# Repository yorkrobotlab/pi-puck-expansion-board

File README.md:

# YRL Expansion Board for the Pi-puck

**An expansion board for the Pi-puck robot platform, including an IMU, XBee socket, navigation switch, RGB LED, and 24-pin Raspberry Pi compatible header.**

See https://github.com/yorkrobotlab/pi-puck for more information on the Pi-puck.

## PCB Layout

## XBee

Scripts to set up the XBee hardware and update the firmware are in [xbee/](xbee/).
Requires the Digi XBee Python Library (see https://github.com/digidotcom/xbee-python).

## Licence

Hardware designs are licensed under a [Creative Commons Attribution-ShareAlike 4.0 International Licence][cc-by-sa].

Unless otherwise specified, software is licensed under an [MIT Licence][mit].

[cc-by-sa]: http://creativecommons.org/licenses/by-sa/4.0/
[mit]: /LICENSE-MIT

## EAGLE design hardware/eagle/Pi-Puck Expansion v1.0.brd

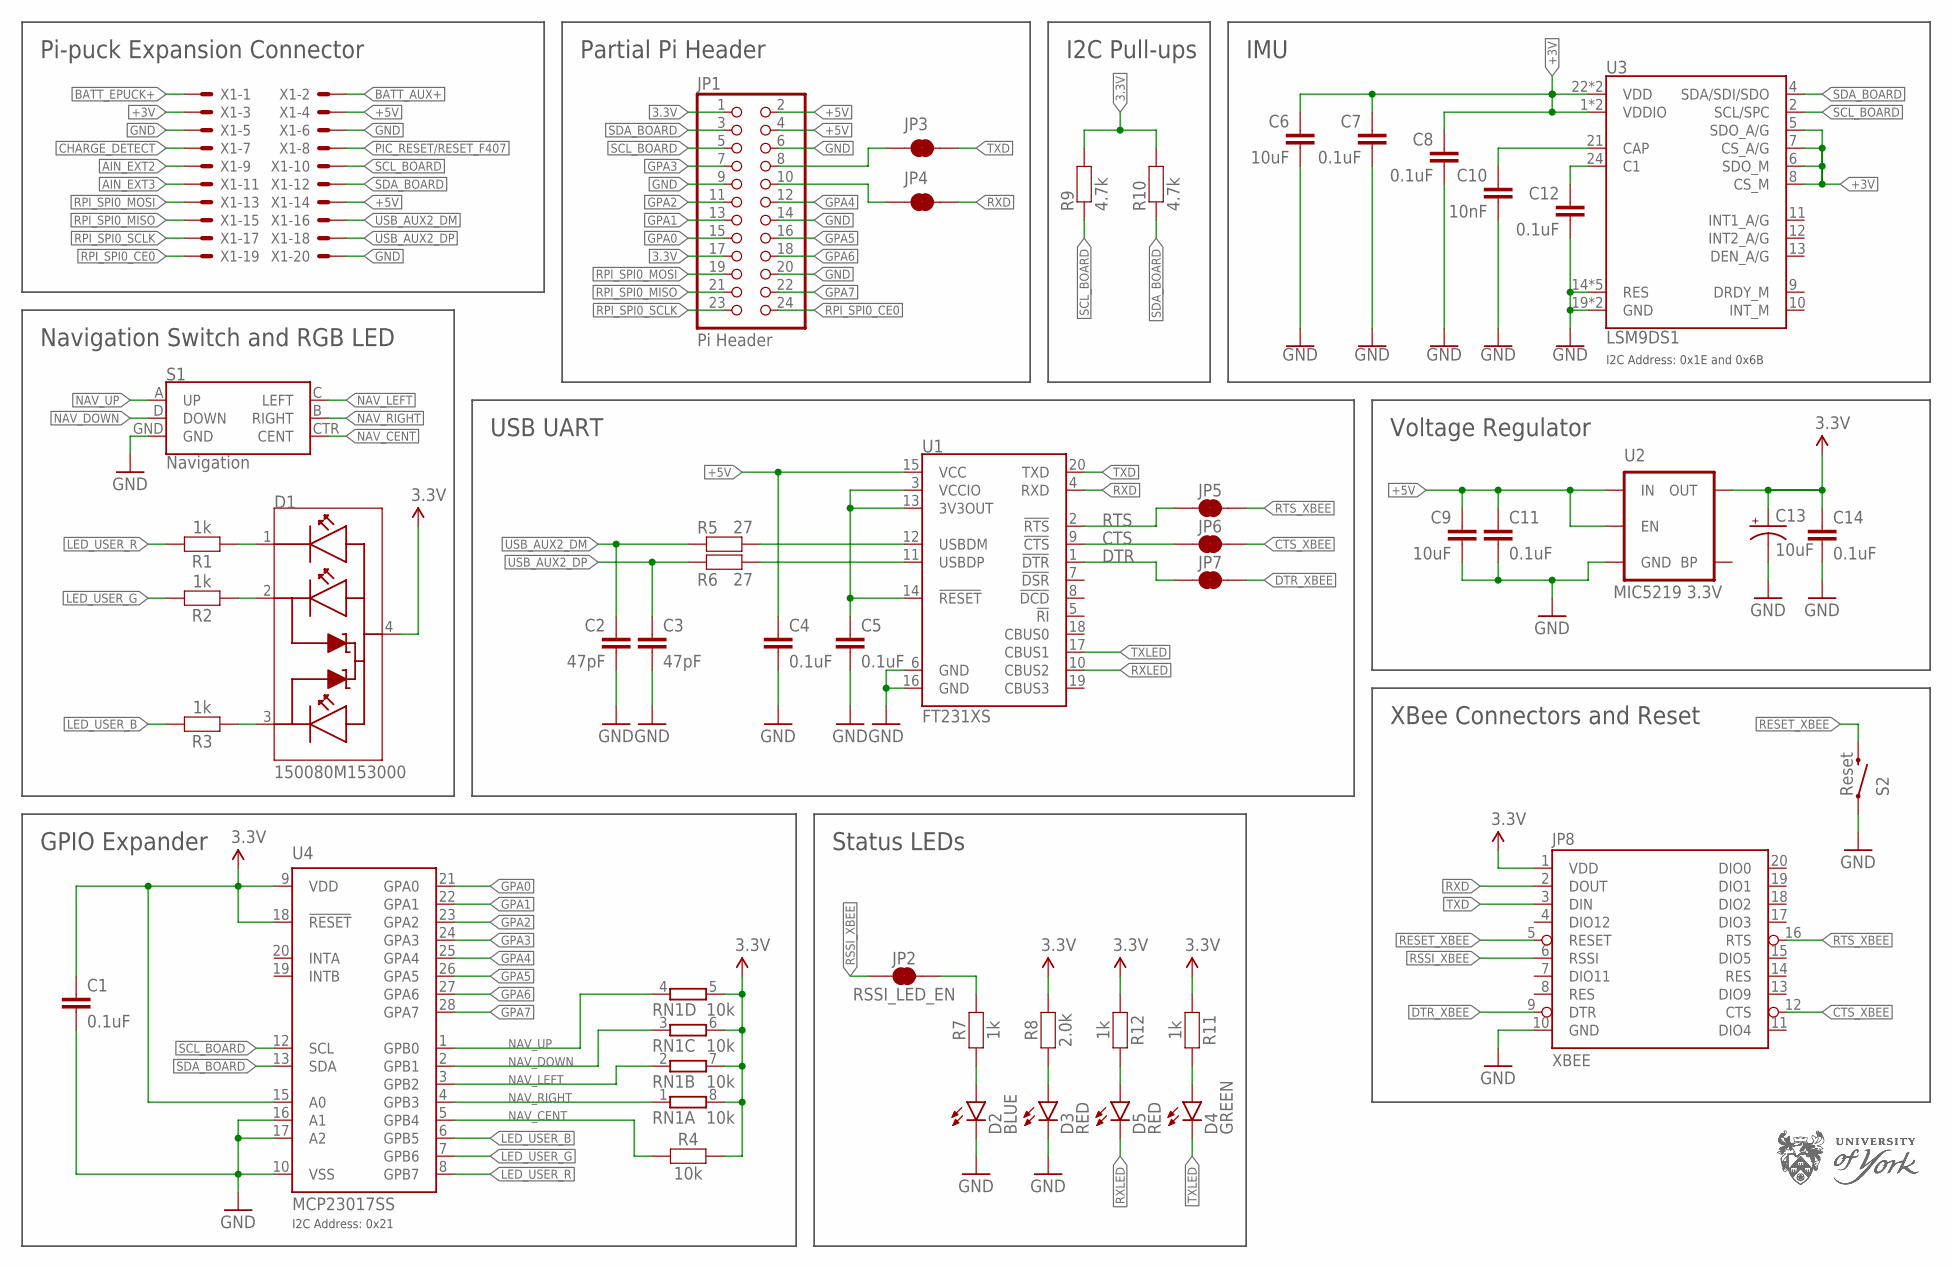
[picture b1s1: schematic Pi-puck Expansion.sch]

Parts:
C1, C4, C5, C7, C8, C11, C12, C14: 0.1uF; 0603
C2, C3: 47pF; 0603
C6, C9: 10uF; 0805
C10: 10nF; 0603
C13: 10uF; EIA3216
D1: 150080M153000; LED_150080M153000
D2: BLUE; LED-0603
D3, D5: RED; LED-0603
D4: GREEN; LED-0603
JP1: Pi Header; 2X12
JP2: RSSI_LED_EN; SMT-JUMPER_2_NC_TRACE_SILK
JP3: TXD; SMT-JUMPER_2_NC_TRACE_SILK
JP4: RXD; SMT-JUMPER_2_NC_TRACE_SILK
JP5: CTS_EN; SMT-JUMPER_2_NC_TRACE_SILK
JP6: RTS_EN; SMT-JUMPER_2_NC_TRACE_SILK
JP7: DTR; SMT-JUMPER_2_NC_TRACE_SILK
JP8: XBEE; XBEE-SILK
LOGO1: UOY-LOGO-30MM; UOY-LOGO-30MM-WIDE
LOGO2: UOY-LOGO-10MM; UOY-LOGO-10MM-WIDE
R1, R2, R3, R7, R11, R12: 1k; 0603
R4: 10k; 0603
R5, R6: 27; 0603
R8: 2.0k; 0603
R9, R10: 4.7k; 0603
RN1: 10k; EXBV8V
S1: Navigation; JOYSTICK_MINI
S2: Reset; TACTILE_SWITCH_SMD_4.6X2.8MM
U1: FT231XS; SSOP20_L
U2: MIC5219 3.3V; SOT23-5
U3: LSM9DS1; LGA24-8X4
U4: MCP23017SS; SSOP28
X1: 87758-2016

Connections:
3.3V: C1.1, C13.+, C14.1, D1.4 (A), JP1.1, JP1.17, JP8.1 (VDD), R4.2, R8.2, R9.2, R10.2, R11.1, R12.1, RN1.5 (2), RN1.6 (2), RN1.7 (2), RN1.8 (2), U2.5 (OUT), U4.9 (VDD), U4.15 (A0), U4.18 (!RESET)
3V-INT: C5.1, U1.3 (VCCIO), U1.13 (3V3OUT), U1.14 (!RESET)
+3V: C6.1, C7.1, C8.1, U3.1 (VDDIO), U3.3 (VDDIO), U3.5 (SDO_A/G), U3.6 (SDO_M), U3.7 (CS_A/G), U3.8 (CS_M), U3.22 (VDD), U3.23 (VDD), X1.3
+5V: C4.1, C9.1, C11.1, JP1.2, JP1.4, U1.15 (VCC), U2.1 (IN), U2.3 (EN), X1.4, X1.14
AIN_EXT2: X1.9
AIN_EXT3: X1.11
BATT_AUX+: X1.2
BATT_EPUCK+: X1.1
C1: C12.1, U3.24 (C1)
CAP: C10.1, U3.21 (CAP)
CHARGE_DETECT: X1.7
CTS: JP6.1, U1.9 (!CTS)
CTS_XBEE: JP6.2, JP8.12 (CTS)
DTR: JP7.1, U1.1 (!DTR)
DTR_XBEE: JP7.2, JP8.9 (DTR)
GND: C1.2, C2.2, C3.2, C4.2, C5.2, C6.2, C7.2, C8.2, C9.2, C10.2, C11.2, C12.2, C13.-, C14.2, D2.C, D3.C, JP1.6, JP1.9, JP1.14, JP1.20, JP8.10 (GND), S1.GND, S2.1, S2.2 (1), U1.6 (GND), U1.16 (GND), U2.2 (GND), U3.14 (RES), U3.15 (RES), U3.16 (RES), U3.17 (RES), U3.18 (RES), U3.19 (GND), U3.20 (GND), U4.10 (VSS), U4.16 (A1), U4.17 (A2), X1.5, X1.6, X1.20
GPA0: JP1.15, U4.21 (GPA0)
GPA1: JP1.13, U4.22 (GPA1)
GPA2: JP1.11, U4.23 (GPA2)
GPA3: JP1.7, U4.24 (GPA3)
GPA4: JP1.12, U4.25 (GPA4)
GPA5: JP1.16, U4.26 (GPA5)
GPA6: JP1.18, U4.27 (GPA6)
GPA7: JP1.22, U4.28 (GPA7)
LED_USER_B: R3.2, U4.6 (GPB5)
LED_USER_G: R2.2, U4.7 (GPB6)
LED_USER_R: R1.2, U4.8 (GPB7)
unnamed: D5.A, R12.2
unnamed: JP1.8, JP3.1
unnamed: JP1.10, JP4.1
unnamed: D4.A, R11.2
unnamed: D1.1 (R), R1.1
unnamed: R6.2, U1.11 (USBDP)
unnamed: R5.2, U1.12 (USBDM)
unnamed: JP2.2, R7.2
unnamed: D1.2 (G), R2.1
unnamed: D1.3 (B), R3.1
unnamed: D3.A, R8.1
NAV_CENT: R4.1, S1.CTR (CENT), U4.5 (GPB4)
NAV_DOWN: RN1.3 (1), S1.D (DOWN), U4.2 (GPB1)
NAV_LEFT: RN1.2 (1), S1.C (LEFT), U4.3 (GPB2)
NAV_RIGHT: RN1.1, S1.B (RIGHT), U4.4 (GPB3)
NAV_UP: RN1.4 (1), S1.A (UP), U4.1 (GPB0)
PIC_RESET/RESET_F407: X1.8
RESET_XBEE: JP8.5 (RESET), S2.3 (2), S2.4 (2)
RPI_SPI0_CE0: JP1.24, X1.19
RPI_SPI0_MISO: JP1.21, X1.15
RPI_SPI0_MOSI: JP1.19, X1.13
RPI_SPI0_SCLK: JP1.23, X1.17
RSSILED: D2.A, R7.1
RSSI_XBEE: JP2.1, JP8.6 (RSSI)
RTS: JP5.1, U1.2 (!RTS)
RTS_XBEE: JP5.2, JP8.16 (RTS)
RXD: JP4.2, JP8.2 (DOUT), U1.4 (RXD)
RXLED: D5.C, U1.10 (CBUS2)
SCL_BOARD: JP1.5, R9.1, U3.2 (SCL/SPC), U4.12 (SCL), X1.10
SDA_BOARD: JP1.3, R10.1, U3.4 (SDA/SDI/SDO), U4.13 (SDA), X1.12
TXD: JP3.2, JP8.3 (DIN), U1.20 (TXD)
TXLED: D4.C, U1.17 (CBUS1)
USB_AUX2_DM: C2.1, R5.1, X1.16
USB_AUX2_DP: C3.1, R6.1, X1.18

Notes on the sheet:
Pi-puck Expansion Connector
Partial Pi Header
GPIO Expander
I2C Address: 0x21
Navigation Switch and RGB LED
I2C Address: 0x1E and 0x6B
Voltage Regulator
I2C Pull-ups
USB UART
IMU
XBee Connectors and Reset
Status LEDs

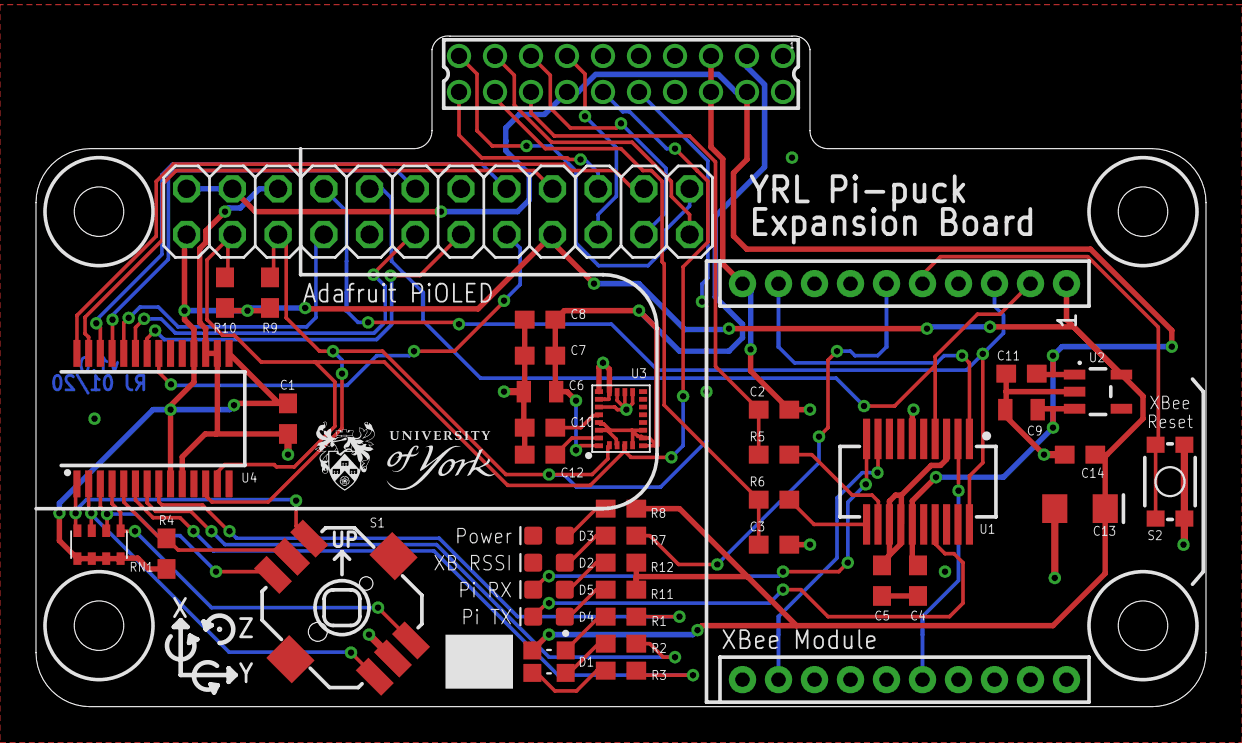
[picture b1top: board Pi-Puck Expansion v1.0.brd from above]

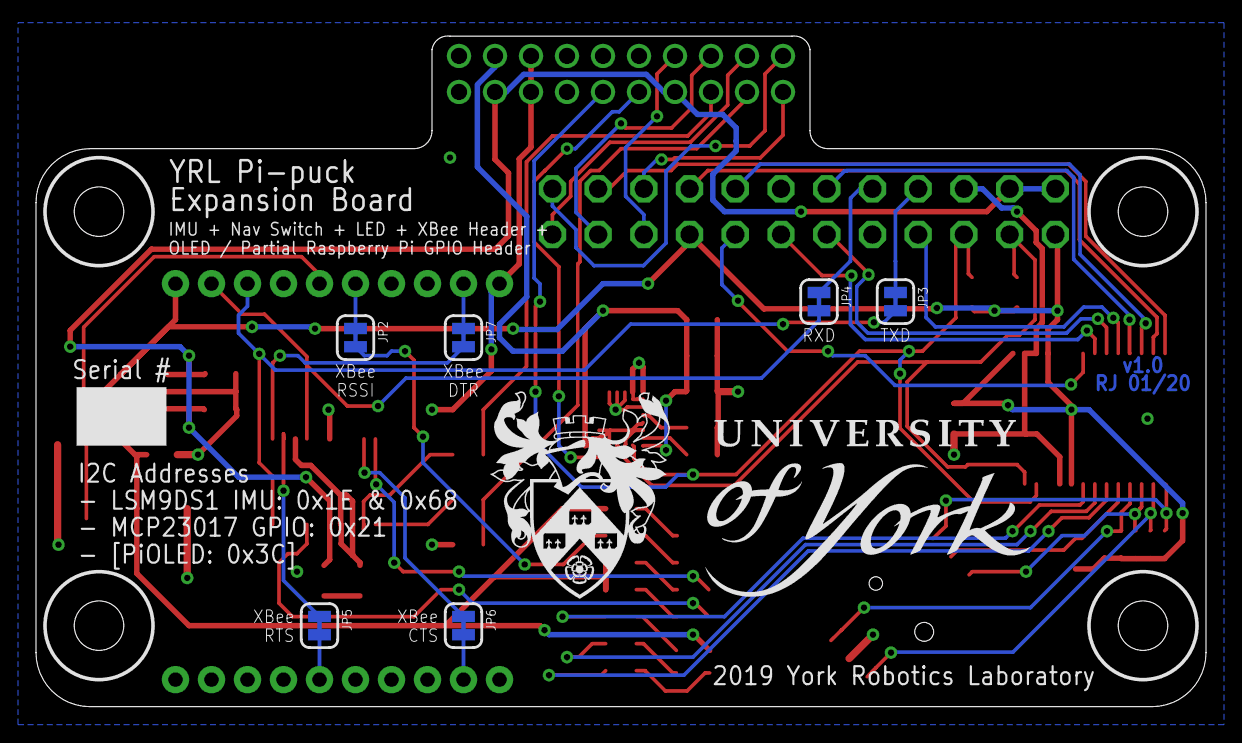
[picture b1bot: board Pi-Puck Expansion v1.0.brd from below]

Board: 2 copper layers, 65.0 x 37.3 mm, 49 parts (7 on the bottom side), 55 nets.

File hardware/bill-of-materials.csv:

Part,Value,Description,Package,Manufacturer,Manufacturer Part Number,Supplier,Order code,Notes,URL
C2,47p,Capacitor,0603,KEMET,C0603X470J1GACTU,Farnell,2905080,±5% C0G / NP0,https://uk.farnell.com/kemet/c0603x470j1gactu/cap-47pf-100v-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
C3,47p,Capacitor,0603,KEMET,C0603X470J1GACTU,Farnell,2905080,±5% C0G / NP0,https://uk.farnell.com/kemet/c0603x470j1gactu/cap-47pf-100v-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
C10,10n,Capacitor,0603,KEMET,C0603X103J8JACTU,Farnell,2579112,±5% U2J,http://uk.farnell.com/kemet/c0603x103j8jactu/capacitor-mlcc-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
C1,0.1u,Capacitor,0603,KEMET,C0603X104K8RACTU,Farnell,2904937,±10% X7R,https://uk.farnell.com/kemet/c0603x104k8ractu/cap-0-1-f-10v-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
C4,0.1u,Capacitor,0603,KEMET,C0603X104K8RACTU,Farnell,2904937,±10% X7R,https://uk.farnell.com/kemet/c0603x104k8ractu/cap-0-1-f-10v-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
C5,0.1u,Capacitor,0603,KEMET,C0603X104K8RACTU,Farnell,2904937,±10% X7R,https://uk.farnell.com/kemet/c0603x104k8ractu/cap-0-1-f-10v-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
C7,0.1u,Capacitor,0603,KEMET,C0603X104K8RACTU,Farnell,2904937,±10% X7R,https://uk.farnell.com/kemet/c0603x104k8ractu/cap-0-1-f-10v-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
C8,0.1u,Capacitor,0603,KEMET,C0603X104K8RACTU,Farnell,2904937,±10% X7R,https://uk.farnell.com/kemet/c0603x104k8ractu/cap-0-1-f-10v-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
C11,0.1u,Capacitor,0603,KEMET,C0603X104K8RACTU,Farnell,2904937,±10% X7R,https://uk.farnell.com/kemet/c0603x104k8ractu/cap-0-1-f-10v-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
C12,0.1u,Capacitor,0603,KEMET,C0603X104K8RACTU,Farnell,2904937,±10% X7R,https://uk.farnell.com/kemet/c0603x104k8ractu/cap-0-1-f-10v-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
C14,0.1u,Capacitor,0603,KEMET,C0603X104K8RACTU,Farnell,2904937,±10% X7R,https://uk.farnell.com/kemet/c0603x104k8ractu/cap-0-1-f-10v-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
C6,10u,Capacitor,0805,KEMET,C0805C106K8PACTU,Farnell,1463362,±10% X5R,https://uk.farnell.com/kemet/c0805c106k8pactu/cap-10-f-10v-1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
C9,10u,Capacitor,0805,KEMET,C0805C106K8PACTU,Farnell,1463362,±10% X5R,https://uk.farnell.com/kemet/c0805c106k8pactu/cap-10-f-10v-1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
C13,10u,Tantalum Capacitor,1206 (EIA 3216–18),KEMET,T491A106K016AT,Farnell,1457414,±10% 16V,https://uk.farnell.com/kemet/t491a106k016at/cap-10-f-16v-10-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
R5,27,Resistor,0603,Panasonic,ERJ3GEYJ270V,Farnell,2059559,,https://uk.farnell.com/panasonic/erj3geyj270v/res-27r-5-0-1w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
R6,27,Resistor,0603,Panasonic,ERJ3GEYJ270V,Farnell,2059559,,https://uk.farnell.com/panasonic/erj3geyj270v/res-27r-5-0-1w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
R1,1k,Resistor,0603,Panasonic,ERJ3GEYJ102V,Farnell,2059601,,https://uk.farnell.com/panasonic/erj3geyj102v/res-1k-5-0-1w-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
R2,1k,Resistor,0603,Panasonic,ERJ3GEYJ102V,Farnell,2059601,,https://uk.farnell.com/panasonic/erj3geyj102v/res-1k-5-0-1w-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
R3,1k,Resistor,0603,Panasonic,ERJ3GEYJ102V,Farnell,2059601,,https://uk.farnell.com/panasonic/erj3geyj102v/res-1k-5-0-1w-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
R7,1k,Resistor,0603,Panasonic,ERJ3GEYJ102V,Farnell,2059601,,https://uk.farnell.com/panasonic/erj3geyj102v/res-1k-5-0-1w-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
R8,1k,Resistor,0603,Panasonic,ERJ3GEYJ102V,Farnell,2059601,,https://uk.farnell.com/panasonic/erj3geyj102v/res-1k-5-0-1w-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
R11,1k,Resistor,0603,Panasonic,ERJ3GEYJ102V,Farnell,2059601,,https://uk.farnell.com/panasonic/erj3geyj102v/res-1k-5-0-1w-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
R12,1k,Resistor,0603,Panasonic,ERJ3GEYJ102V,Farnell,2059601,,https://uk.farnell.com/panasonic/erj3geyj102v/res-1k-5-0-1w-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
R9,4.7k,Resistor,0603,Panasonic,ERJ3GEYJ472V,Farnell,2059619,,https://uk.farnell.com/panasonic/erj3geyj472v/res-4k7-5-0-1w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
R10,4.7k,Resistor,0603,Panasonic,ERJ3GEYJ472V,Farnell,2059619,,https://uk.farnell.com/panasonic/erj3geyj472v/res-4k7-5-0-1w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
R4,10k,Resistor,0603,Panasonic,ERJ3GEYJ103V,Farnell,2059627,,http://uk.farnell.com/panasonic-electronic-components/erj3ge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
RN1,10k,Array Chip Resistor,EXBV8V,Panasonic,EXBV8V103JV,Farnell,2060167,,https://uk.farnell.com/panasonic/exbv8v103jv/resistor-ccav-a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
D3,,Red LED,0603,Kingbright,KPT-1608LVSECK-J3-PRV,Farnell,2610406,,https://uk.farnell.com/kingbright/kpt-1608lvseck-j3-prv/led-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
D5,,Red LED,0603,Kingbright,KPT-1608LVSECK-J3-PRV,Farnell,2610406,,https://uk.farnell.com/kingbright/kpt-1608lvseck-j3-prv/led-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
D4,,Green LED,0603,Kingbright,KPT-1608LVZGCK,Farnell,2610409,,https://uk.farnell.com/kingbright/kpt-1608lvzgck/led-green-5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
D2,,Blue LED,0603,Kingbright,KPT-1608LVVBC-D,Farnell,2610410,,https://uk.farnell.com/kingbright/kpt-1608lvvbc-d/led-blue-2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
D1,,RGB LED,0805,Würth Elektronik,150080M153000,Farnell,2764966,,https://uk.farnell.com/wurth-elektronik/150080m153000/led-re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
S1,,Small Tactile Joystick w/ Select Switch,SMD with guide bosses,Multicomp,MCMT5-F-V,Farnell,1316987,,https://uk.farnell.com/multicomp/mcmt5-f-v/navigation-switch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
S2,,Momentary Switch (Pushbutton) - SPST,KMR2 (SMD 4.6x2.8mm),C & K Components,KMR221NG LFS,Farnell,2845727,Maybe change to grounded version next time,https://uk.farnell.com/c-k-components/kmr221ng-lfs/tactile-s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
U1,,FT231X USB-UART Converter,SSOP-20,FTDI,FT231XS-R,Farnell,2081328,,https://uk.farnell.com/ftdi/ft231xs/i-f-usb2-0-fs-to-f-l-h-s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
U2,,3.3V voltage regulator,SOT23-5,Microchip,MIC5219-3.3YM5-TR,Farnell,2510252,,https://uk.farnell.com/microchip/mic5219-3-3ym5-tr/ldo-0-5vd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
U3,,LSM9DS1 9DoF IMU,LGA-24,ST Microelectronics,LSM9DS1TR,Farnell,2532383,,https://uk.farnell.com/stmicroelectronics/lsm9ds1tr/mems-acc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
U4,,I2C 16-bit GPIO Expander,SSOP-28,Microchip,MCP23017-E/SS,Farnell,1467674,On schematic as MCP23017SS,http://uk.farnell.com/microchip/mcp23017-e-ss/ic-io-expander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

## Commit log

2020-02-25 Added hardware design, and some info into the readme file
2020-02-25 Updated PCB layout images to include ground planes
2020-02-25 Updated schematic PDF and renamed Eagle design files
2020-02-27 Added Creative Commons licence for hardware designs
2020-02-28 Added MIT licence for any software code
2020-06-19 Added XBee set-up and firmware update Python scripts

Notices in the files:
parts and their libraries:
SparkFun-RF: Licensing: Creative Commons ShareAlike 4.0 International - https://creativecommons.org/licenses/by-sa/4.0
